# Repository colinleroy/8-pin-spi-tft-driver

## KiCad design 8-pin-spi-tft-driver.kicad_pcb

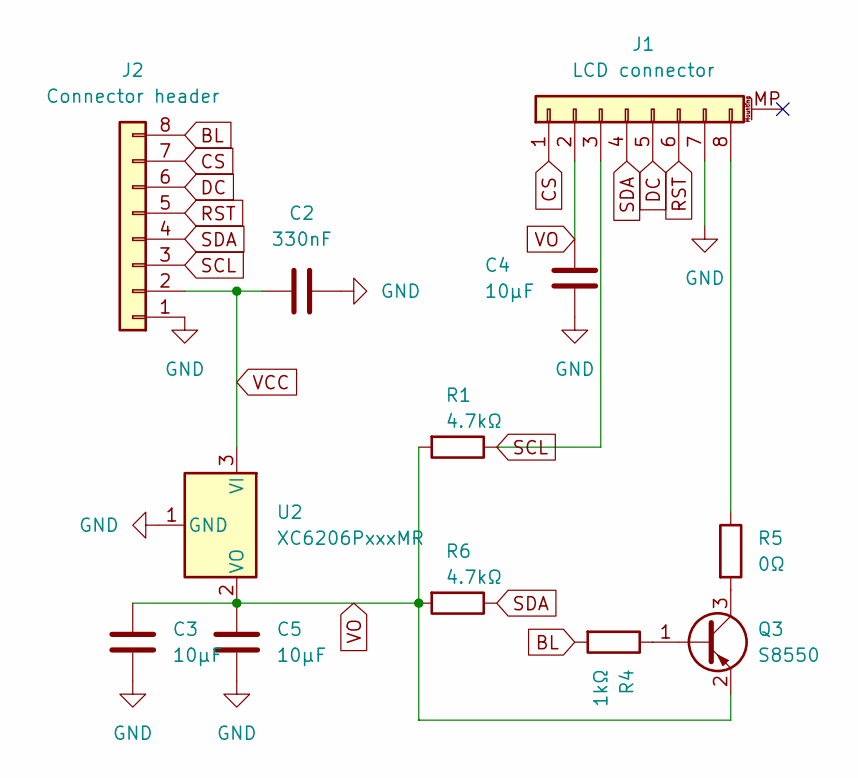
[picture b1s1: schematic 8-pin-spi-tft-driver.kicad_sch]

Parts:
C2: 330nF; C_0603_1608Metric; LCSC C1615
C3, C4, C5: 10µF; C_0603_1608Metric; LCSC C19702
J1: LCD connector; TE_0-1734839-8_1x08-1MP_P0.5mm_Horizontal; LCSC C19267907
J2: Connector header; PinHeader_1x08_P2.54mm_Vertical
Q3: S8550; SOT-23-3; LCSC C2147
R1, R6: 4.7kΩ; R_0603_1608Metric; LCSC C23162
R4: 1kΩ; R_0603_1608Metric; LCSC C21190
R5: 0Ω; R_0603_1608Metric; LCSC C21189
U2: XC6206PxxxMR; SOT-23-3; LCSC C347376

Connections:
BL: J2.8, R4.2
CS: J1.1, J2.7
DC: J1.5, J2.6
GND: C2.2, C3.1, C4.2, C5.2, J1.7, J2.1, U2.1 (GND)
unnamed: J1.8, R5.1
unnamed: Q3.1 (B), R4.1
unnamed: Q3.3 (C), R5.2
RST: J1.6, J2.5
SCL: J1.3, J2.3, R1.1
SDA: J1.4, J2.4, R6.1
VCC: C2.1, J2.2, U2.3 (VI)
VO: C3.2, C4.1, C5.1, J1.2, Q3.2 (E), R1.2, R6.2, U2.2 (VO)

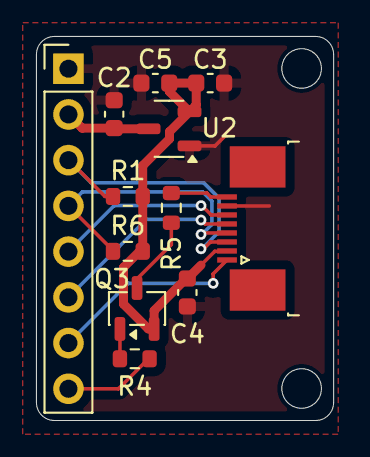
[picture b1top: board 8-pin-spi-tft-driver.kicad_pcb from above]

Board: 2 copper layers, 16.5 x 21.3 mm, 12 parts (0 on the bottom side), 12 nets.
